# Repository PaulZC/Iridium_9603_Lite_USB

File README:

#########################
# Iridium 9603 Lite USB #
#########################

An untested design for a very small, lightweight, USB-powered Iridium 9603 satellite communication module.
Dimensions are 35mm x 44mm x 18mm and the populated PCB will weigh close to 33g (including the antenna).

Python 2.7 code has been tested on Windows 10 and Debian Linux (Raspberry Pi).

The USB interface is provided by a Cypress CY7C65213 USB-UART Bridge.

Power for the Iridium 9603 is provided by a Linear Technology LTC3225EDDB supercapacitor charger.

See Iridium_9603_Lite_USB.pdf for a full description of the project:
https://github.com/PaulZC/Iridium_9603_Lite_USB/blob/master/Iridium_9603_Lite_USB.pdf

The Python code can be found in Iridium_9603_Lite_USB.py
https://github.com/PaulZC/Iridium_9603_Lite_USB/blob/master/Iridium_9603_Lite_USB.py

The PCB schematic, layout and bill of materials can be found in:
https://github.com/PaulZC/Iridium_9603_Lite_USB/blob/master/Iridium_9603_Lite_USB_V1.pdf

The Eagle files can be found in:
https://github.com/PaulZC/Iridium_9603_Lite_USB/tree/master/Eagle/V1

Iridium_9603_Lite_USB.cyusb contains the configuration file for Cypress' USB Serial Configuration Utility.

This project is distributed under a Creative Commons Attribution + Share-alike (BY-SA) licence.

Enjoy!

Paul

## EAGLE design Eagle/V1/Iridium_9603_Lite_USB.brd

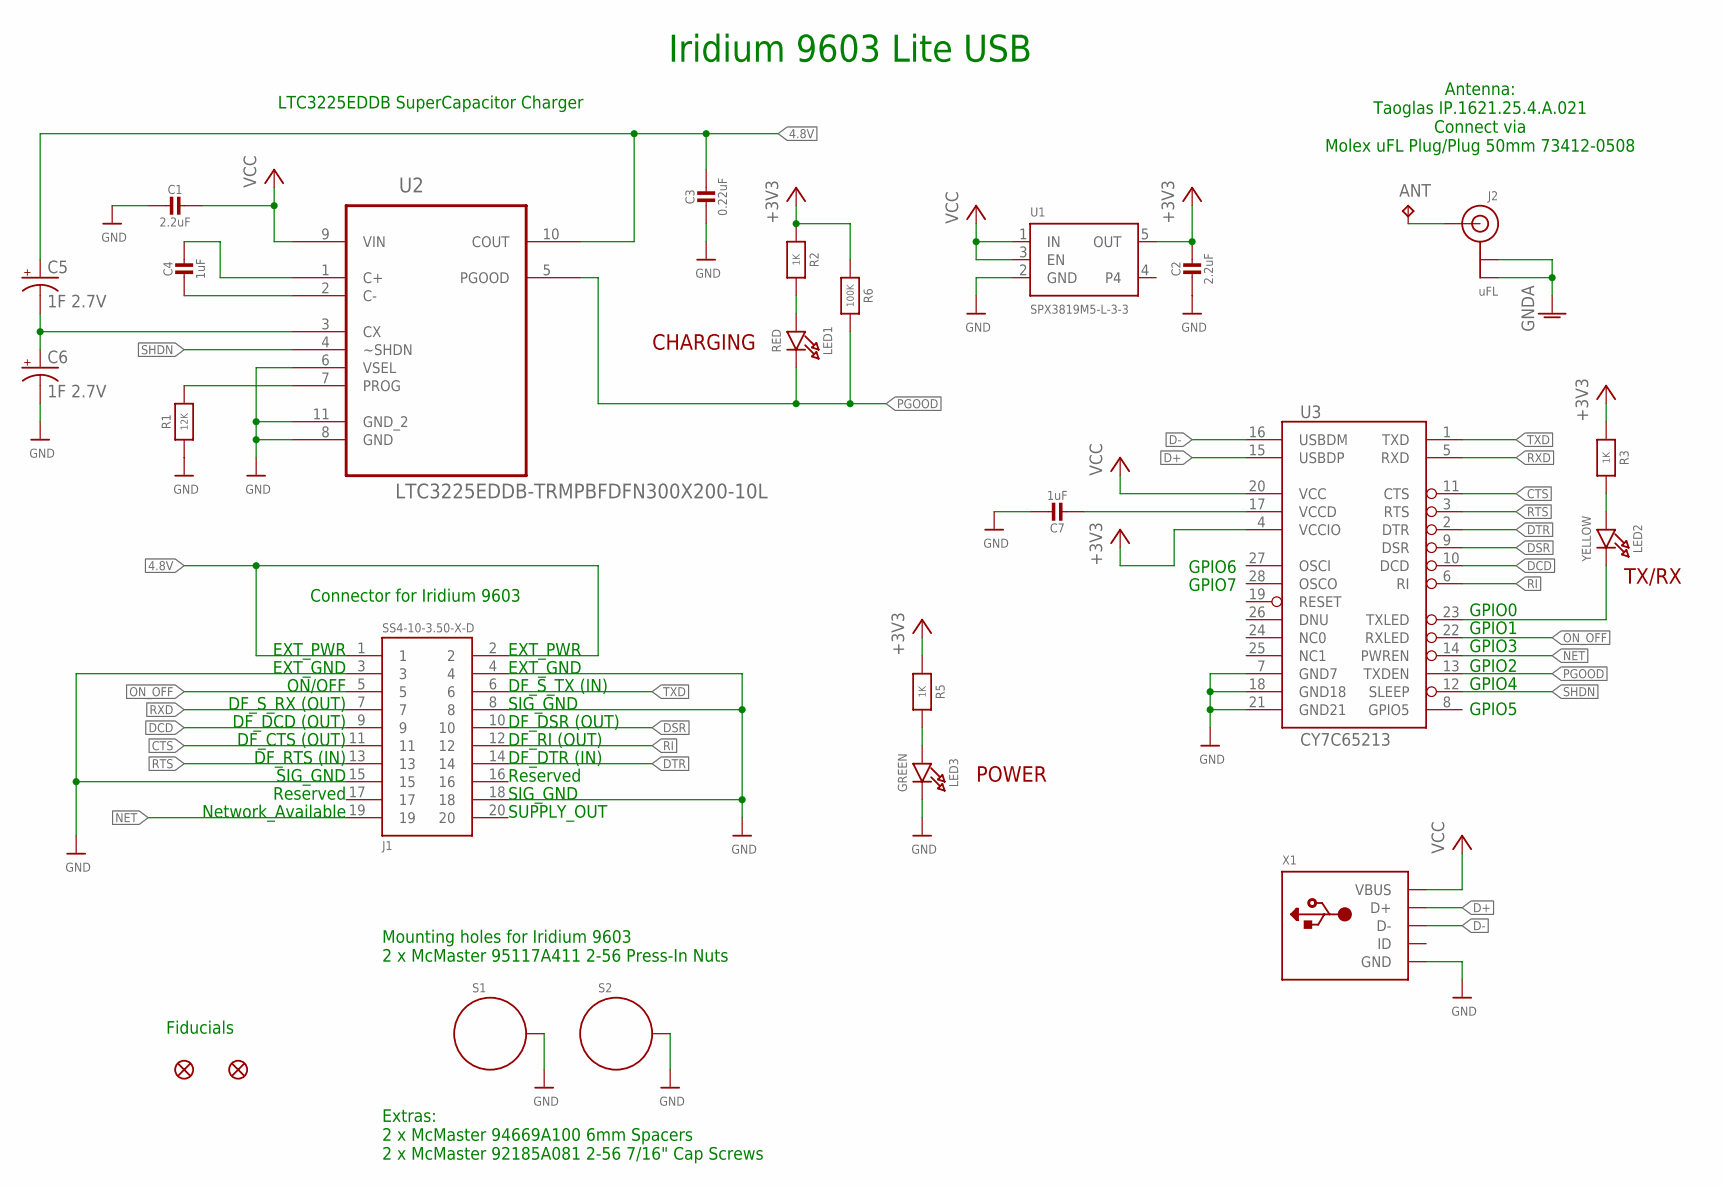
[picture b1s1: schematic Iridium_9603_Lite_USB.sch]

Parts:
ANT: TPB2,54; B2,54
C1, C2: 2.2uF; 0805-NO
C3: 0.22uF; 0603-NO
C4, C7: 1uF; 0603-NO
C5, C6: 1F 2.7V; CPOL-RADIAL-1F-2.7V
FD1, FD2: FIDUCIAL1X2; FIDUCIAL-1X2
J1: SS4-10-3.50-X-D
J2: uFL; U.FL
LED1: RED; CHIPLED_0805_NOOUTLINE
LED2: YELLOW; CHIPLED_0805_NOOUTLINE
LED3: GREEN; CHIPLED_0805_NOOUTLINE
R1: 12K; 0805-NO
R2, R3, R5: 1K; 0603-NO
R6: 100K; 0603-NO
S1, S2: STANDOFF_ELECTRICALMCMASTER-95117A411; STANDOFF-ELECTRICAL-MCMASTER-95117A411
U1: SPX3819M5-L-3-3; SOT23-5
U2: LTC3225EDDB-TRMPBFDFN300X200-10L; DFN300X200-10L
U3: CY7C65213; SSOP28DB
X1: USBFCI_10103594_MILL; FCI_10103594_MILL

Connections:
4.8V: C3.1, C5.+, J1.1, J1.2, U2.10 (COUT)
+3V3: C2.1, R2.1, R3.1, R5.1, R6.1, U1.5 (OUT), U3.4 (VCCIO)
ANT: ANT.TP, J2.3 (SIGNAL)
CTS: J1.11, U3.11 (CTS)
D+: U3.15 (USBDP), X1.D+
D-: U3.16 (USBDM), X1.D-
DCD: J1.9, U3.10 (DCD)
DSR: J1.10, U3.9 (DSR)
DTR: J1.14, U3.2 (DTR)
GND: C1.2, C2.2, C3.2, C6.-, C7.1, J1.3, J1.4, J1.8, J1.15, J1.18, LED3.C, R1.1, S1.P1, S2.P1, U1.2 (GND), U2.6 (VSEL), U2.8 (GND), U2.11 (GND_2), U3.7 (GND7), U3.18 (GND18), U3.21 (GND21), X1.BASE@1 (GND), X1.BASE@2 (GND), X1.GND, X1.SPRT@1 (GND), X1.SPRT@2 (GND), X1.SPRT@3 (GND), X1.SPRT@4 (GND)
GNDA: J2.1 (GND), J2.2 (GND)
unnamed: LED2.A, R3.2
unnamed: C7.2, U3.17 (VCCD)
unnamed: LED1.A, R2.2
unnamed: LED2.C, U3.23 (TXLED)
unnamed: C5.-, C6.+, U2.3 (CX)
unnamed: LED3.A, R5.2
unnamed: C4.2, U2.2 (C-)
unnamed: C4.1, U2.1 (C+)
unnamed: R1.2, U2.7 (PROG)
NC1: U3.25 (NC1)
NET: J1.19, U3.14 (PWREN)
ON_OFF: J1.5, U3.22 (RXLED)
PGOOD: LED1.C, R6.2, U2.5 (PGOOD), U3.13 (TXDEN)
RI: J1.12, U3.6 (RI)
RTS: J1.13, U3.3 (RTS)
RXD: J1.7, U3.5 (RXD)
SHDN: U2.4 (~SHDN), U3.12 (SLEEP)
TXD: J1.6, U3.1 (TXD)
VCC: C1.1, U1.1 (IN), U1.3 (EN), U2.9 (VIN), U3.20 (VCC), X1.VBUS

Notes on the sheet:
Connector for Iridium 9603
Mounting holes for Iridium 9603 2 x McMaster 95117A411 2-56 Press-In Nuts
Iridium 9603 Lite USB
EXT_PWR
EXT_GND
ON/OFF
DF_S_RX (OUT)
DF_DCD (OUT)
DF_CTS (OUT)
DF_RTS (IN)
SIG_GND
Reserved
Network_Available
DF_S_TX (IN)
DF_DSR (OUT)
DF_RI (OUT)
DF_DTR (IN)
SUPPLY_OUT
Fiducials
Antenna: Taoglas IP.1621.25.4.A.021 Connect via Molex uFL Plug/Plug 50mm 73412-0508
Extras: 2 x McMaster 94669A100 6mm Spacers 2 x McMaster 92185A081 2-56 7/16" Cap Screws
LTC3225EDDB SuperCapacitor Charger
GPIO0
GPIO1
GPIO3
GPIO2
GPIO4
GPIO5
GPIO6
GPIO7
CHARGING
POWER
TX/RX

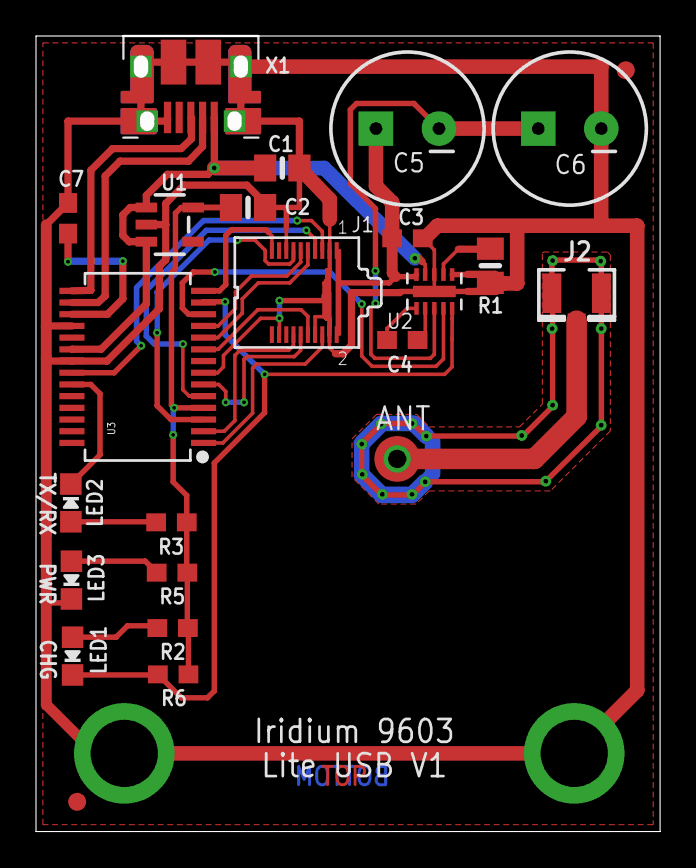
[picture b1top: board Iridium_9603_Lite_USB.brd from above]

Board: 2 copper layers, 33.9 x 43.4 mm, 26 parts (0 on the bottom side), 29 nets.

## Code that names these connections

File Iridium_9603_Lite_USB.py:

# Iridium 9603 Lite USB

# Tested with Python 2.7 on Windows 10 64-Bit

# Tested with Python 2.7 on Linux (Raspberry Pi) using
# https://github.com/PaulZC/python-ucdev

# 9603 power is provided by LTC3225 supercapacitor charger (charged from USB port)
# 9603 module is interfaced via a Cypress CY7C65213:
# GPIO_0 is Tx/Rx LED
# GPIO_1 is connected to 9603 ON_OFF (High=On Low=Off)
# GPIO_4 is connected to LTC3225 SHDN (High=On Low=Off)
# LTC3225 PGOOD is connected to GPIO_2 (High = Power Is Good)
# 9603 Network Available is connected to GPIO_3 (High = Network Is Available)
# All eight UART signals are connected (TXD, RXD, RTS, CTS, DTR, DSR, DCD, RI)

import serial
import time
from cy7c65213 import CyUSBSerial, CyGPIO

# Define serial port
# Check Device Manager for the correct port name (on Windows)
serport = 'COM1'
# Linux (ls /dev/tty*)
#serport = '/dev/ttyACM0'

# Point to the DLL provided by Cypress
# Windows
dll = "C:\\Program Files (x86)\\Cypress\\USB-Serial SDK\\library\\cyusbserial\\x64\\cyusbserial.dll"
# Linux
#dll = "/usr/local/lib/libcyusbserial.so"

# CY7C65213 Pin Definitions
ON_pin      = 1 # 9603 ON/OFF = GPIO_1
PGOOD_pin   = 2 # LTC3225 PGOOD = GPIO_2
NET_pin     = 3 # 9603 Network Available = GPIO_3
SHDN_pin    = 4 # LTC3225 Shutdown = GPIO_4

class IridiumUSBport(object):
    
    def __init__(self):
        print 'Opening GPIO...'
        # Load DLL provided by Cypress (Windows notation)
        self.dll = dll
        self.lib = CyUSBSerial(lib = self.dll)
        #self.dev = self.lib.find().next() # Use first device found
        self.dev = self.lib.find(vid=0x04B4,pid=0x0003).next() # Look for a specific vendor and product id
        # Access GPIO
        self.gpio = CyGPIO(self.dev)
        self.ON_pin = self.gpio.pin(ON_pin) # 9603 ON/OFF = GPIO_1
        self.PGOOD_pin = self.gpio.pin(PGOOD_pin) # LTC3225 PGOOD = GPIO_2
        self.NET_pin = self.gpio.pin(NET_pin) # 9603 Network Available = GPIO_3
        self.SHDN_pin = self.gpio.pin(SHDN_pin) # LTC3225 Shutdown = GPIO_4
        
        print 'Opening serial port...'
        self.ser = serial.Serial(serport,19200,timeout=1)

        self.CSQ = int(0)
        self.MOF = int(0)
        self.MTF = int(0)
        self.MOS = int(0)
        self.MTS = int(0)
        self.MTQ = int(0)
        
    def writeAndWait(self, data, exp):
        print 'Writing ' + data + ' Expecting ' + exp
        self.ser.write(data+'\r')
        for i in range(30):
            resp = self.ser.readline()
            if resp != '':
                if data in resp:
                    print resp[:-1]
                if exp in resp:
                    print resp[:-1]
                    break
        return resp[:-1]

    def queueMessage(self, mesg):
        print 'Queueing: ' + mesg
        self.ser.write('AT+SBDWT='+mesg+'\r')
        result = False
        for i in range(30):
            resp = self.ser.readline()
            if resp != '':
                if 'SBDWT' in resp: # AT+SBDWT is returned _after_ the OK!
                    print resp[:-1]
                    break
                if 'OK' in resp:
                    print resp[:-1]
                    result = True
                    #break
                if 'ERROR' in resp:
                    print resp[:-1]
                    break
        return result

    def initiateSBD(self):
        print 'Initiating SBD session!'
        resp = self.writeAndWait('AT+SBDI','SBDI:')
        try:
            resp_list = resp.split(",")
            mos = int(resp_list[0][-1])
            mts = int(resp_list[2][-1])
            mtq = int(resp_list[5][1:])
        except:
            mos = int(0)
            mts = int(0)
            mtq = int(0)
        self.MOS = mos
        self.MTS = mts
        self.MTQ = mtq

    def readSBD(self):
        print 'Reading text message...'
        self.ser.write('AT+SBDRT\r')
        msg = ''
        seq = 0
        for i in range(30):
            resp = self.ser.readline()
            if resp != '':
                if (seq == 2) and ('OK' in resp):
                    break
                elif (seq == 1):
                    msg = resp[:-2]
                    seq = 2
                elif (seq == 0) and ('SBDRT:' in resp):
                    seq = 1
        return msg
        
    def set_RTS(self, rts):
        self.ser.setRTS(rts)

    def set_DTR(self, dtr):
        self.ser.setDTR(dtr)

    def set_SHDN(self, shdn):
        self.SHDN_pin.set(shdn)

    def set_ON(self, onoff):
        self.ON_pin.set(onoff)

    def get_CTS(self):
        return self.ser.getCTS()

    def get_DSR(self):
        return self.ser.getDSR()

    def get_DCD(self):
        return self.ser.getDCD()

    def get_RI(self):
        return self.ser.getRI()

    def get_PGOOD(self):
        return self.PGOOD_pin.get()

    def get_NET(self):
        return self.NET_pin.get()

    def check_CSQ(self):
        resp = self.writeAndWait('AT+CSQ','CSQ:')
        try:
            csq = int(resp[-2])
        except:
            csq = int(0)
        self.CSQ = csq

    def check_SBDS(self):
        resp = self.writeAndWait('AT+SBDS','SBDS:')
        try:
            resp_list = resp.split(",")
            mof = int(resp_list[0][-1])
            mtf = int(resp_list[2][-1])
        except:
            mof = int(0)
            mtf = int(0)
        self.MOF = mof
        self.MTF = mtf

    def close(self):
        print 'Closing port...'
        self.ser.close()

try:
    # Create object and open port
    ip = IridiumUSBport()

    # Set On/Off low to disable 9603 while supercapacitor charges
    ip.set_ON(0)

    # Set Shutdown high to enable LTC3225
    ip.set_SHDN(1)

    # Set RTS and DTR low
    ip.set_RTS(1) # 1 = Low
    ip.set_DTR(1) # 1 = Low

    # Keep reading PGOOD (GPIO_2) until it goes high
    pgood = ip.get_PGOOD()
    while pgood == 0:
        print 'Waiting for PGOOD to go high...'
        pgood = ip.get_PGOOD()
        time.sleep(1)

    # Now enable 9603
    ip.set_ON(1)
    time.sleep(2)

    # Send ATtention code - response should be 'OK'
    ip.writeAndWait('AT','OK')

    # Enable Echo - response should be 'OK'
    ip.writeAndWait('ATE1','OK')

    # Ignore DTR - response should be 'OK'
    ip.writeAndWait('AT&D0','OK')

    # Disable flow control - response should be 'OK'
    ip.writeAndWait('AT&K0','OK')

    # Set SBD session timeout to 300 seconds
    ip.writeAndWait('AT+SBDST=300','OK')

    # Clear mobile originated message buffer - just in case!
    ip.writeAndWait('AT+SBDD0','OK')

    # Try for 300 seconds to get a CSQ of 5
    for i in range(100):

        # Check signal quality
        ip.check_CSQ()
        print 'CSQ is '+str(ip.CSQ)

        # If CSQ == 5 then move on
        if ip.CSQ == 5: break

        # Wait
        time.sleep(3)

    # If CSQ == 5, queue a message, initiate SBD session
    if ip.CSQ == 5:

        # Add a new Mobile Originated message to the queue
        # Comment the next two lines out if you don't want to send a message
        #  and only want to check for new Mobile Terminated messages
        message = 'This is a test message!'
        ip.queueMessage(message)
        
        ip.initiateSBD()
        if ip.MOS == 0: print 'No message to send...'
        if ip.MOS == 1: print 'MESSAGE SENT!'
        if ip.MOS == 2: print 'SEND ERROR!'
        if ip.MTS == 0: print 'No message to receive...'
        if ip.MTS == 2: print 'RECEIVE ERROR!'
        if ip.MTS == 1:
            print 'MESSAGE RECEIVED!'
            msg = ip.readSBD()
            print msg
            try:
                fp = open('Iridium_Rx_Log.txt','ab') # Append message to Iridium_Rx_Log.txt
                fp.write(msg+'\r\n')
                fp.close()
            except:
                print 'FILE WRITE ERROR!'
        print 'MTQ is',ip.MTQ

    # Clear mobile originated message buffer - just in case!
    ip.writeAndWait('AT+SBDD0','OK')

except KeyboardInterrupt:

    print 'Ctrl-C Received!'

finally:
    # Send 'Flush to Eeprom' - response should be 'OK'
    ip.writeAndWait('AT*F','OK')
    time.sleep(2)

    # 9603 is now ready to be powered down
    ip.set_ON(0) # Turn 9603 off
    ip.set_SHDN(0) # Disable LTC3225
    time.sleep(2)

    # Close port
    ip.close()

    print 'Bye!'

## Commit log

2017-03-09 :lollipop: Added .gitattributes & .gitignore files
2017-03-18 Updated ANT and GNDA to provide impedance of 50 Ohms
2017-04-02 Added support for Linux (Debian on Raspberry Pi)

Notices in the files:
parts and their libraries:
microbuilder: This work is placed in the public domain, and may be freely used for commercial and non-commercial work with the following conditions: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
SparkFun-Electromechanical: Licensing: Creative Commons ShareAlike 4.0 International - https://creativecommons.org/licenses/by-sa/4.0
